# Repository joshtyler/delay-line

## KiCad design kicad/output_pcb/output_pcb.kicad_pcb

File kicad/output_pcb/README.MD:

Lattice_iCE_FPGA.lib is from https://github.com/xesscorp/KiCad-Schematic-Symbol-Libraries

kifield -x output_pcb.sch fpga.sch -i output_pcb_fields.csv
Swap fields to go the other way

Errata:
v1.0 - BAT54s diode is backwards, remedy is solder upside down.

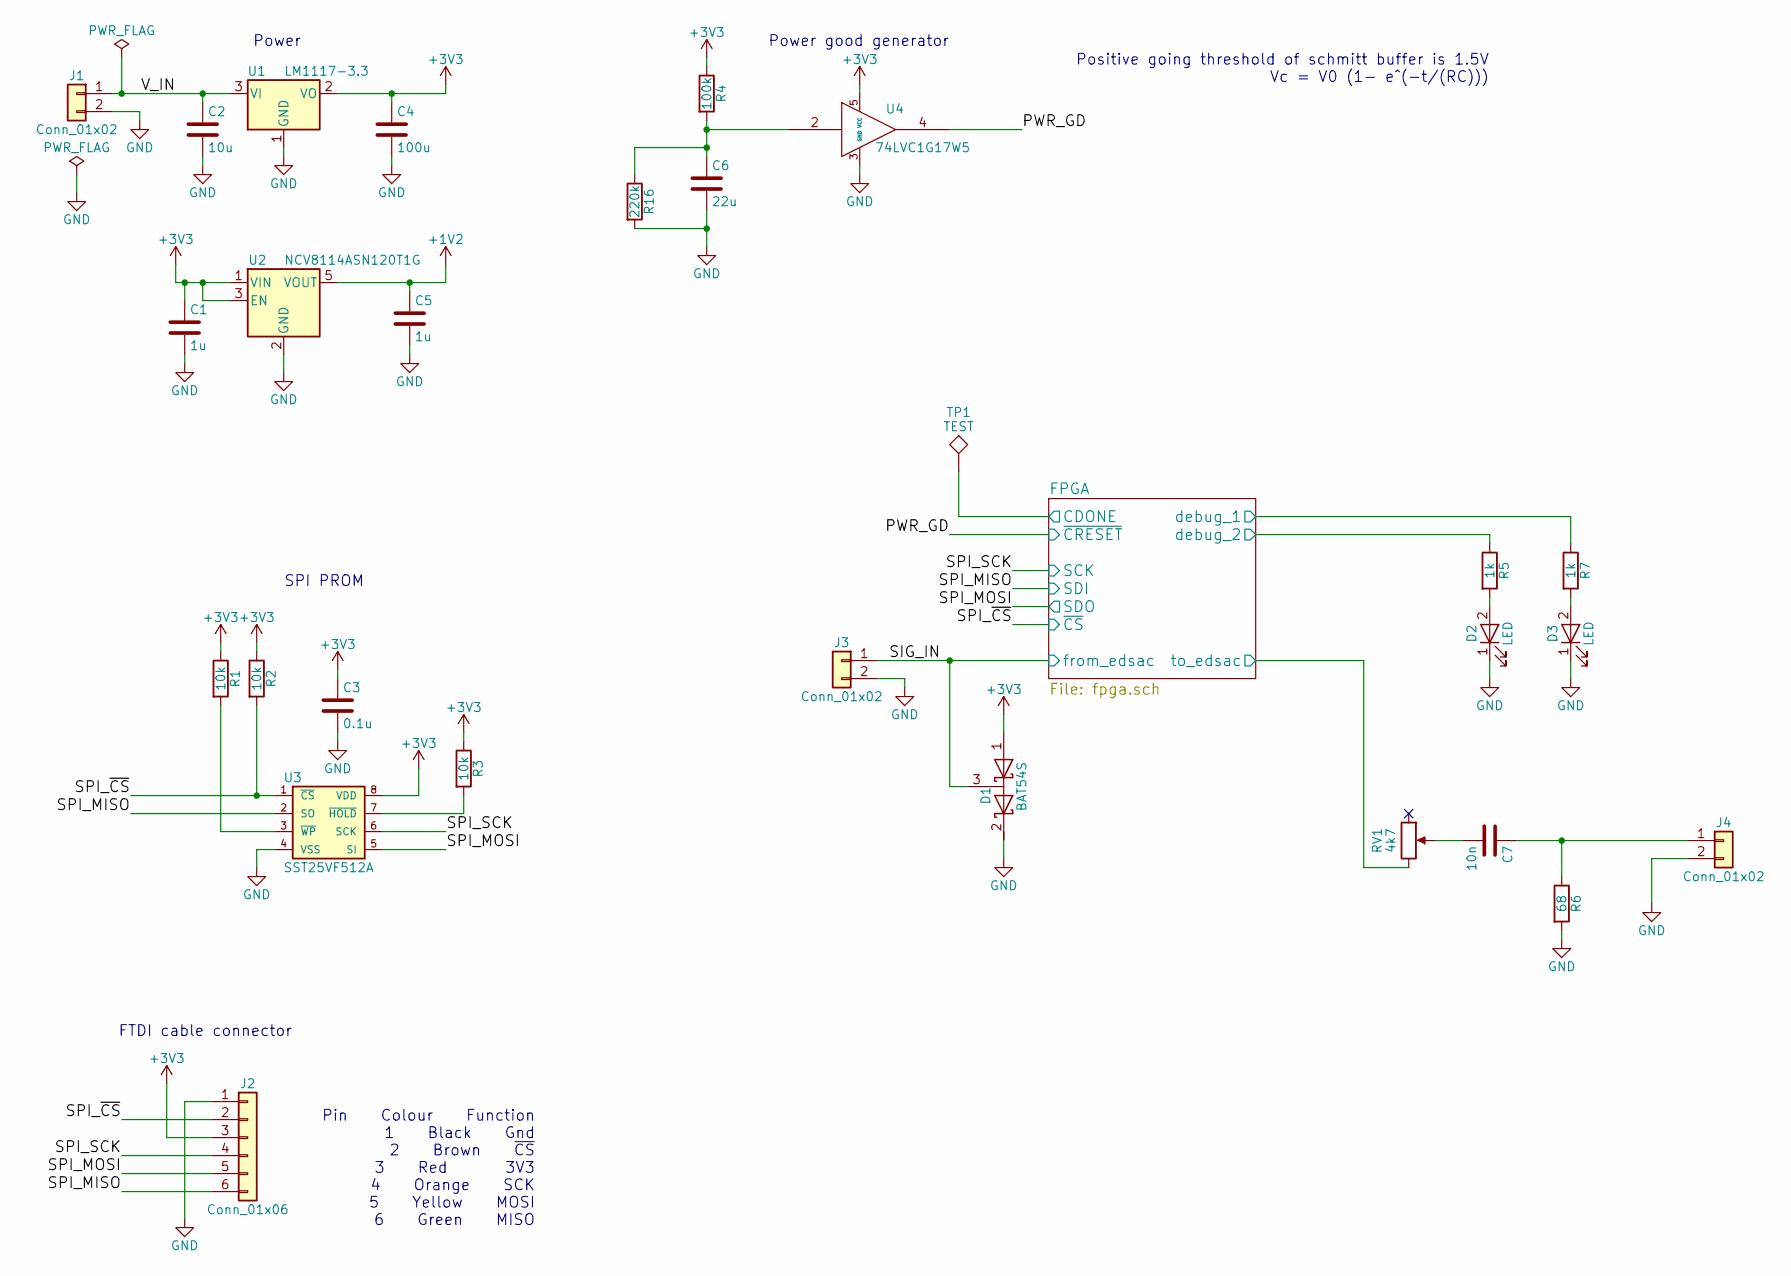
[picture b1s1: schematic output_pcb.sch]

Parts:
C1, C5: 1u; C_0603_HandSoldering
C2: 10u; C_0805_HandSoldering
C3: 0.1u; C_0603_HandSoldering
C4: 100u; C_1210_HandSoldering
C6: 22u; C_0603_HandSoldering
C7: 10n; C_0603_HandSoldering
D1: BAT54S; SOT-23_Handsoldering
D2, D3: LED; D_0603
J1, J3, J4: Conn_01x02; SMA_THT_Jack_Straight
J2: Conn_01x06; Molex_KK-6410-06_06x2.54mm_Straight
R1, R2, R3: 10k; R_0603_HandSoldering
R4: 100k; R_0603_HandSoldering
R5, R7: 1k; R_0603_HandSoldering
R6: 68; R_0603_HandSoldering
R16: 220k; R_0603_HandSoldering
RV1: 4k7; Potentiometer_Trimmer_ACP_CA9v_Horizontal_Px10.0mm_Py5.0mm
TP1: TEST; Test_Point_Pad_d1.5mm
U1: LM1117-3.3; SOT-223-3_TabPin2
U2: NCV8114ASN120T1G; SOT-23-5
U3: SST25VF512A; SOIC-8_3.9x4.9mm_Pitch1.27mm
U4: 74LVC1G17W5; SOT-23-5

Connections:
+1V2: C5.1, U2.5 (VOUT); also elsewhere on the board
/FPGA/CDONE: TP1.1; also elsewhere on the board
/FPGA/debug_1: R7.1; also elsewhere on the board
/FPGA/debug_2: R5.1; also elsewhere on the board
/FPGA/to_edsac: RV1.3; also elsewhere on the board
/PWR_GD: U4.4; also elsewhere on the board
/SIG_IN: D1.3 (common), J3.1; also elsewhere on the board
/SPI_MISO: J2.6, U3.2 (SO); also elsewhere on the board
/SPI_MOSI: J2.5, U3.5 (SI); also elsewhere on the board
/SPI_SCK: J2.4, U3.6 (SCK); also elsewhere on the board
/SPI_~CS: J2.2, R2.2, U3.1 (~CS); also elsewhere on the board
/V_IN: C2.1, J1.1, U1.3 (VI)
GND: C1.2, C2.2, C3.2, C4.2, C5.2, C6.2, D1.2 (K), D2.1 (K), D3.1 (K), J1.2, J2.1, J3.2, J4.2, R6.2, R16.2, U1.1 (GND), U2.2 (GND), U3.4 (VSS), U4.3 (GND); also elsewhere on the board
unnamed: C6.1, R4.2, R16.1, U4.2
unnamed: C7.1, J4.1, R6.1
unnamed: C7.2, RV1.2
unnamed: D2.2 (A), R5.2
unnamed: D3.2 (A), R7.2
unnamed: R1.2, U3.3 (~WP)
unnamed: R3.2, U3.7 (~HOLD)

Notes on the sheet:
FTDI cable connector
SPI PROM
Pin Colour Function 1 Black Gnd 2 Brown ~CS~ 3 Red 3V3 4 Orange SCK 5 Yellow MOSI 6 Green MISO
Power
Power good generator
Positive going threshold of schmitt buffer is 1.5V Vc = V0 (1- e^(-t/(RC)))

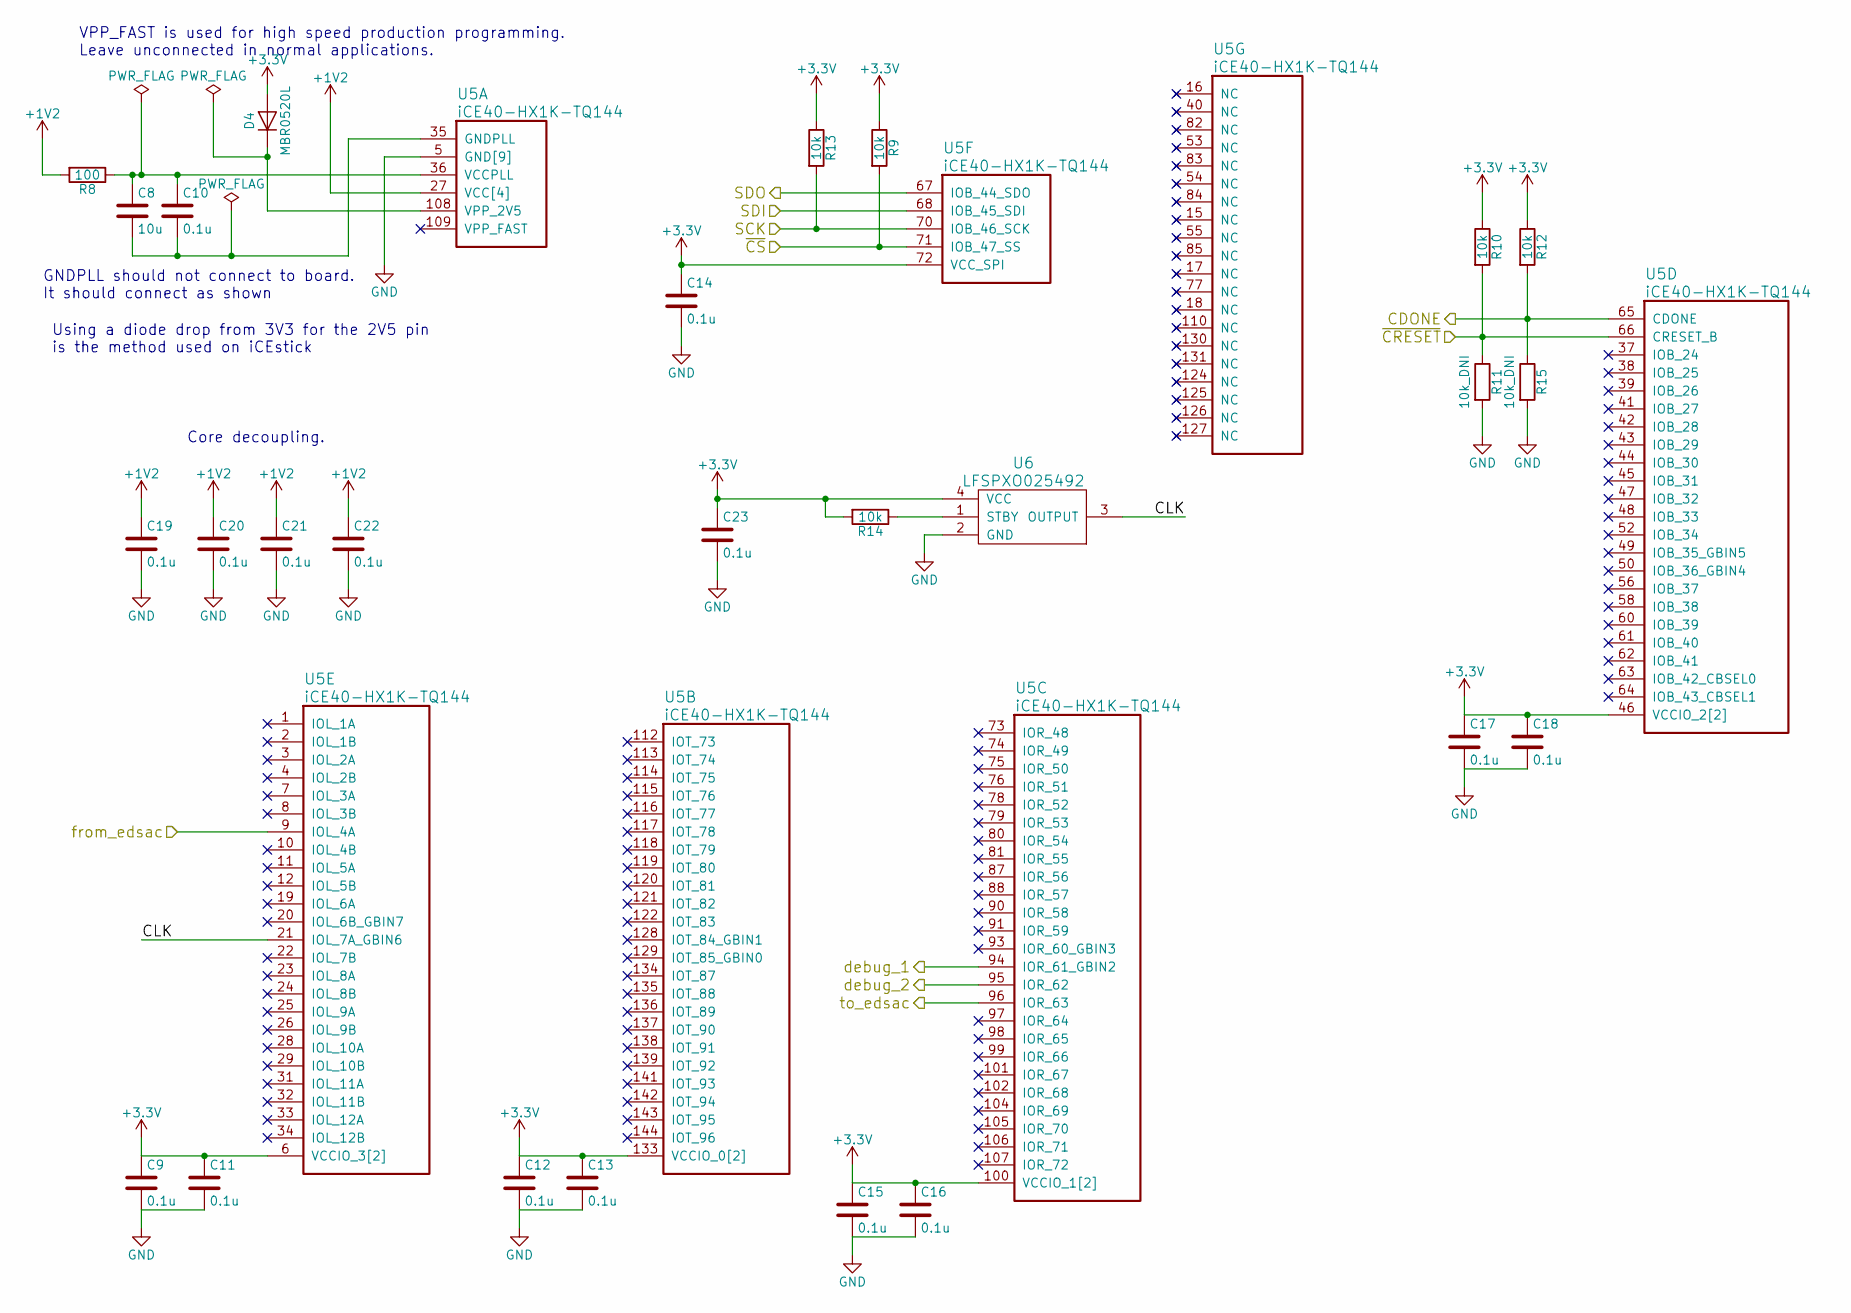
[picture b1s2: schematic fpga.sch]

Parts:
C8: 10u; C_0805_HandSoldering
C9, C10, C11, C12, C13, C14, C15, C16, C17, C18, C19, C20, C21, C22, C23: 0.1u; C_0603_HandSoldering
D4: MBR0520L; D_SOD-123
R8: 100; R_0603_HandSoldering
R9, R10, R12, R13, R14: 10k; R_0603_HandSoldering
R11, R15: 10k_DNI; R_0603_HandSoldering
U5: iCE40-HX1K-TQ144; TQFP-144_20x20mm_Pitch0.5mm
U6: LFSPXO025492; Crystal_SMD_3225-4pin_3.2x2.5mm

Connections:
+1V2: C19.1, C20.1, C21.1, C22.1, R8.2, U5.27 (VCC[4]), U5.51 (VCC[4]), U5.92 (VCC[4]), U5.111 (VCC[4]); also elsewhere on the board
/FPGA/CDONE: R12.2, R15.1, U5.65 (CDONE); also elsewhere on the board
/FPGA/CLK: U5.21 (IOL_7A_GBIN6), U6.3 (OUTPUT)
/FPGA/debug_1: U5.94 (IOR_61_GBIN2); also elsewhere on the board
/FPGA/debug_2: U5.95 (IOR_62); also elsewhere on the board
/FPGA/to_edsac: U5.96 (IOR_63); also elsewhere on the board
/PWR_GD: R10.2, R11.1, U5.66 (CRESET_B); also elsewhere on the board
/SIG_IN: U5.9 (IOL_4A); also elsewhere on the board
/SPI_MISO: U5.68 (IOB_45_SDI); also elsewhere on the board
/SPI_MOSI: U5.67 (IOB_44_SDO); also elsewhere on the board
/SPI_SCK: R13.2, U5.70 (IOB_46_SCK); also elsewhere on the board
/SPI_~CS: R9.2, U5.71 (IOB_47_SS); also elsewhere on the board
GND: C9.2, C11.2, C12.2, C13.2, C14.2, C15.2, C16.2, C17.2, C18.2, C19.2, C20.2, C21.2, C22.2, C23.2, R11.2, R15.2, U5.5 (GND[9]), U5.13 (GND[9]), U5.14 (GND[9]), U5.59 (GND[9]), U5.69 (GND[9]), U5.86 (GND[9]), U5.103 (GND[9]), U5.132 (GND[9]), U5.140 (GND[9]), U6.2 (GND); also elsewhere on the board
unnamed: C8.1, C10.1, R8.1, U5.36 (VCCPLL)
unnamed: C8.2, C10.2, U5.35 (GNDPLL)
unnamed: D4.1 (K), U5.108 (VPP_2V5)
unnamed: R14.1, U6.1 (STBY)

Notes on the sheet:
VPP_FAST is used for high speed production programming. Leave unconnected in normal applications.
Using a diode drop from 3V3 for the 2V5 pin is the method used on iCEstick
GNDPLL should not connect to board. It should connect as shown
Core decoupling.

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
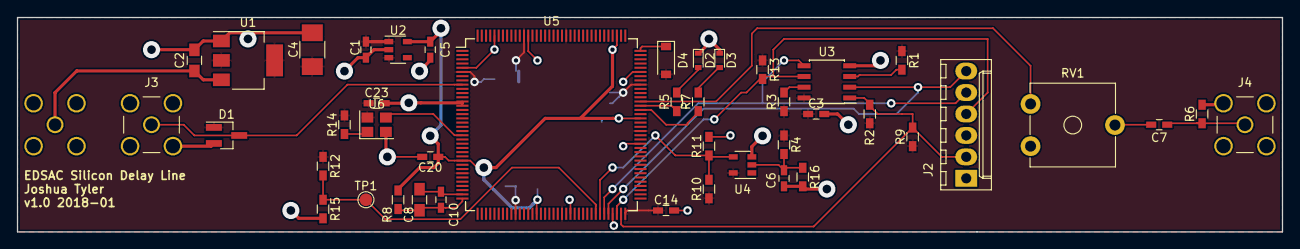
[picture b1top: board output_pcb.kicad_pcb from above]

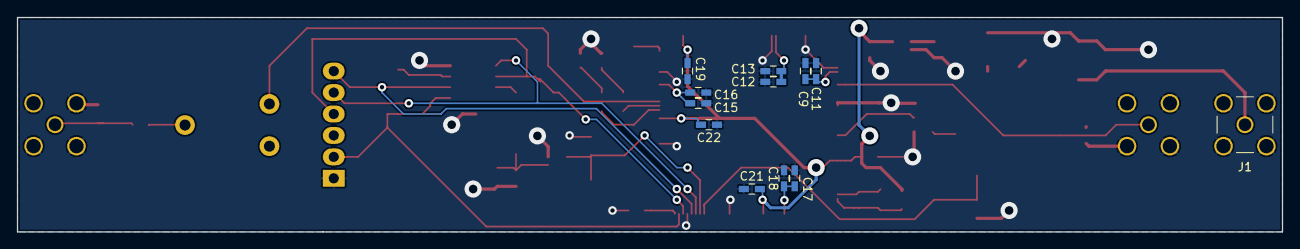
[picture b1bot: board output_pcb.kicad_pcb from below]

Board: 2 copper layers, 149.9 x 25.4 mm, 55 parts (12 on the bottom side), 26 nets.

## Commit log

2017-06-06 Initial commit. FIFO working in basic sim
2017-06-06 Add icecube project, and move to makefile
2017-06-06 Pulse generator working
2017-06-07 All modules present
2017-06-07 Working in sim. Wont synth due to use of time keyword
2017-06-07 Synthesising and passing all timing
2017-06-12 Restructure
2017-06-12 Blank report
2017-06-12 Added abstract and bibliography to empty template
2017-06-12 Working Acronyms
2017-06-12 Fix small caps style
2017-06-12 ToC draft
2017-06-13 Pre move to ModelSim
2017-06-13 Add ModelSim project
2017-06-13 Improved delay_line testbench now working
2017-06-13 Post synth sim not working - Lattice models don't workgit status
2017-06-13 Attempting two pronged approach - VHDL and Verilog Lattice SIM models
2017-06-13 Lattice simulation models still do not workgit status
2017-06-14 UART Simulation working
2017-06-14 UART loopback not working
2017-06-14 Pre remove non-zero initialisation values for Lattice toolchain
2017-06-14 TX only UART test working
2017-06-14 UART loopback working
2017-06-15 Controller partially complete. Added python constant generator
2017-06-15 controller written, not tested
2017-06-16 Controller tests successfully
2017-06-19 Memory manager working correctly in tb
2017-06-19 Move away from iverilog sim
2017-06-19 Genericise components, and move testbenches to SV
2017-06-19 Delay line de-inital valued and working in sim
2017-06-19 Added and tested message assembler and disassembler
2017-06-19 Update test_delay_line to remove timescale
2017-06-20 Pre move to different memory manager system
2017-06-21 Project now compiles well. Beginning work on PC application
2017-06-21 Pre move away from own Cpp wrapper towards standard wrapper
2017-06-21 Still not working with libftdi cpp bindings!
2017-06-21 Basic FTDI driver working
2017-06-21 Able to send start request and receive response
2017-06-22 Message generator generating Cpp and Python successfully
2017-06-23 Moving to CLion
2017-06-26 mem_gui getting there. Pre change up FTDI read/write API
2017-06-26 Working. Now to add GUI
2017-06-26 Single button GUI working
2017-06-27 Beginning work on GUI
2017-06-29 Gui mostly working. Pre redo getters/setters for class objects in Python
2017-06-29 Seems to be working. Pre architecture change
2017-07-03 Combined model works correctly. Pre-move to pure verilog
2017-07-06 Lattice tools are still not cooperating and producing a working implementation of test harness. I will move this project to Xilinx
2017-07-07 Working delay line. Updating GUI
2017-07-12 Test harness working, and GUI improved
2017-07-20 Pre cleanup
2017-07-20 Cleaned up
2017-07-20 Clean delay line files a little
2017-07-20 Add tristate to delay line
2017-07-20 Clean up
2017-07-25 pre modify transformer schematic
2017-07-26 Working two transformer system
2017-07-28 pre move to separate components
2017-07-29 Main circuit working well
2017-08-04 At stage of ordering parts.
2017-08-09 Written more of the report
2017-08-10 Move test_harness to icestorm
2017-08-10 Move icestorm projects to makefile
2017-08-10 Remove old toolchains
2017-08-10 Added tristate to test_harness, and meets timing Haven't simulated this build
2017-08-23 Report writing sesh
2017-08-23 Made the first half of the report make more sense
2017-08-28 Working in the tube!
2017-08-28 Started demonstration slides
2017-08-29 Drawn FPGA architecture diagram
2017-08-29 Added test harness diagrams
2017-08-29 More report progress
2017-08-30 Minor fix to mem_gui, and demo slides are done
2017-08-30 Pre move to separate testing and verification
2017-08-30 Remove misc directory as it is not needed
2017-08-30 Remove SPICE misc folder
2017-08-31 Pre re-factor Gantt
2017-09-06 Part way through first proof read.
2017-09-07 All diagrams now OK
2017-09-07 Printing draft
2017-09-07 Final. To submit
2018-01-27 Ordered output PCB - v1.0
2018-05-28 SPI Prog now working with single bit write
2018-07-05 Working basic program small array
2018-07-05 Working large transfer to eeprom
2018-08-28 Working spi programmer
2018-08-29 Greatly improved CLI
2018-09-10 Add output pcb bringup
2020-02-09 First steps towards adding support for SPI programming over wishbone FPGA component
2020-02-09 Replace depreacted header
2020-02-09 Plumbed in framework for choosing target
